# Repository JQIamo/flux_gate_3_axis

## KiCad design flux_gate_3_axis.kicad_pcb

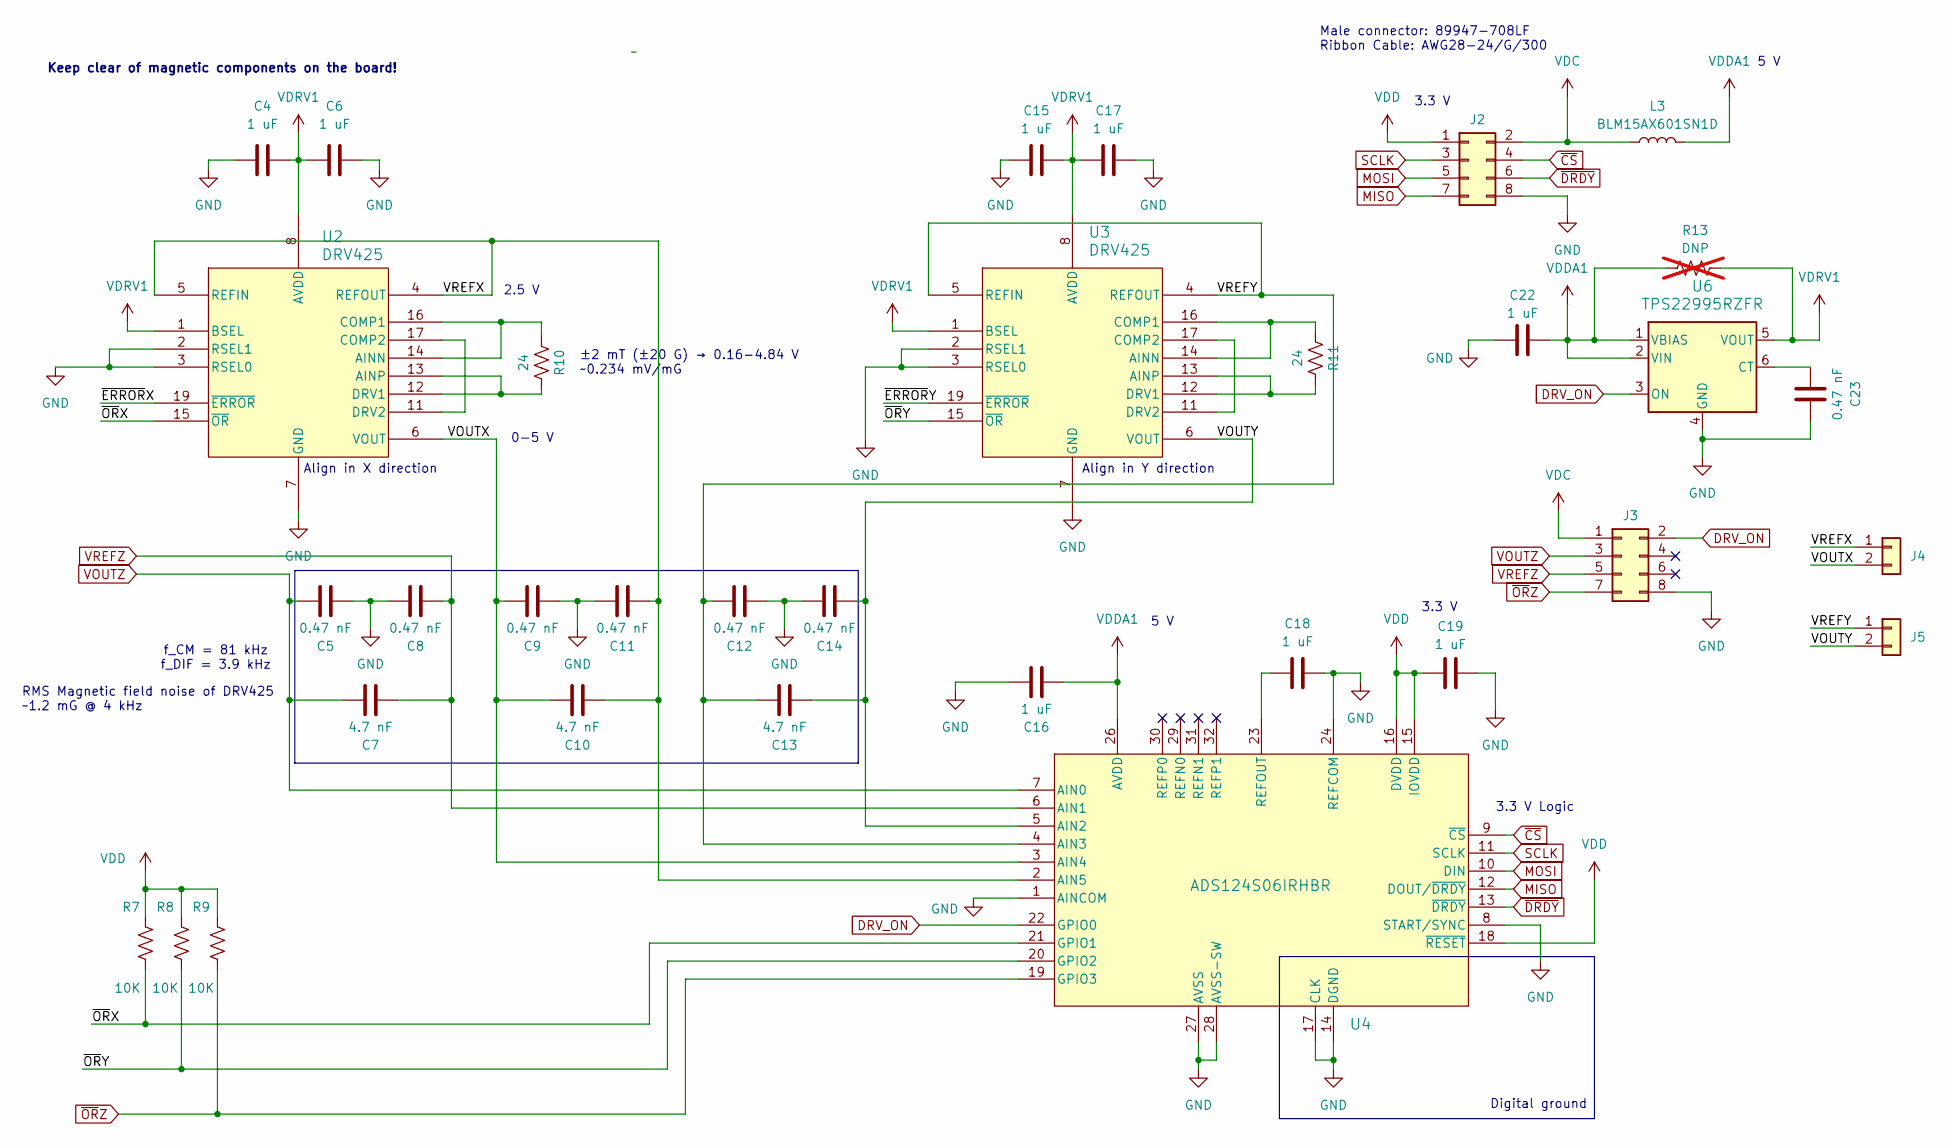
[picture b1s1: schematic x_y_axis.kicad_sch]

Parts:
C4, C6, C15, C16, C17, C18, C19, C22: 1 uF; C_0402_1005Metric; Digikey 490-10018-1-ND
C5, C8, C9, C11, C12, C14, C23: 0.47 nF; C_0402_1005Metric; Digikey 490-1297-1-ND
C7, C10, C13: 4.7 nF; C_0402_1005Metric; Digikey 490-GRM1555C1H472GE01DCT-ND
J2: Conn_02x04_Odd_Even; AMPHENOL_98464-G61-08LF; Digikey 609-6027-ND
J3: Conn_02x04_Odd_Even; PinHeader_2x04_P2.00mm_Vertical; Digikey A108094-ND
J4, J5: Conn_01x02; TestPoint_2Pads_Pitch2.54mm_Drill0.8mm
L3: BLM15AX601SN1D; L_0402_1005Metric; Digikey 490-5441-1-ND
R7, R8, R9: 10K; R_0402_1005Metric; Digikey 311-10KJRCT-ND
R10, R11: 24; R_0805_2012Metric; Digikey 13-RT0805BRD0724RLCT-ND
R13: DNP; R_0402_1005Metric; not fitted
U2, U3: DRV425; WQFN20_RTJ_TEX; Digikey 296-DRV425QWRTJRQ1CT-ND
U4: ADS124S06IRHBR; VQFN-32-1EP_5x5mm_P0.5mm_EP3.1x3.1mm; Digikey 296-ADS124S06IRHBRCT-ND
U6: TPS22995RZFR; WQFN6_RZF_TEX

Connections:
/x_y_axis/VOUTX: C9.1, C10.1, J4.2, U2.6 (VOUT), U4.3 (AIN4)
/x_y_axis/VOUTY: C13.2, C14.2, J5.2, U3.6 (VOUT), U4.5 (AIN2)
/x_y_axis/VREFX: C10.2, C11.2, J4.1, U2.4 (REFOUT), U2.5 (REFIN), U4.2 (AIN5)
/x_y_axis/VREFY: C12.1, C13.1, J5.1, U3.4 (REFOUT), U3.5 (REFIN), U4.4 (AIN3)
/x_y_axis/~ERRORX: U2.19 (~ERROR)
/x_y_axis/~ERRORY: U3.19 (~ERROR)
/x_y_axis/~ORX: R7.1, U2.15 (~OR), U4.21 (GPIO1)
/x_y_axis/~ORY: R8.1, U3.15 (~OR), U4.20 (GPIO2)
DRV_ON: J3.2, U4.22 (GPIO0), U6.3 (ON); also elsewhere on the board
GND: C4.1, C5.2, C6.1, C8.1, C9.2, C11.1, C12.2, C14.1, C15.1, C16.1, C17.1, C18.2, C19.2, C22.2, C23.1, J2.8, J3.8, U2.2 (RSEL1), U2.3 (RSEL0), U2.7 (GND), U2.10 (GND), U2.18 (GND), U2.20 (GND), U2.21 (GND), U3.2 (RSEL1), U3.3 (RSEL0), U3.7 (GND), U3.10 (GND), U3.18 (GND), U3.20 (GND), U3.21 (GND), U4.1 (AINCOM), U4.8 (START/SYNC), U4.14 (DGND), U4.17 (CLK), U4.24 (REFCOM), U4.27 (AVSS), U4.28 (AVSS-SW), U4.33 (PAD), U6.4 (GND); also elsewhere on the board
MISO: J2.7, U4.12 (DOUT/~DRDY); also elsewhere on the board
MOSI: J2.5, U4.10 (DIN); also elsewhere on the board
unnamed: R10.2, U2.14 (AINN), U2.16 (COMP1)
unnamed: R10.1, U2.12 (DRV1), U2.13 (AINP)
unnamed: U2.11 (DRV2), U2.17 (COMP2)
unnamed: R11.2, U3.14 (AINN), U3.16 (COMP1)
unnamed: R11.1, U3.12 (DRV1), U3.13 (AINP)
unnamed: U3.11 (DRV2), U3.17 (COMP2)
unnamed: C18.1, U4.23 (REFOUT)
unnamed: C23.2, U6.6 (CT)
SCLK: J2.3, U4.11 (SCLK); also elsewhere on the board
VDC: J2.2, J3.1, L3.2; also elsewhere on the board
VDD: C19.1, J2.1, R7.2, R8.2, R9.2, U4.15 (IOVDD), U4.16 (DVDD), U4.18 (~RESET); also elsewhere on the board
VDDA1: C16.2, C22.1, L3.1, R13.1, U4.26 (AVDD), U6.1 (VBIAS), U6.2 (VIN)
VDRV1: C4.2, C6.2, C15.2, C17.2, R13.2, U2.1 (BSEL), U2.8 (AVDD), U2.9 (AVDD), U3.1 (BSEL), U3.8 (AVDD), U3.9 (AVDD), U6.5 (VOUT)
VOUTZ: C5.1, C7.1, J3.3, U4.7 (AIN0); also elsewhere on the board
VREFZ: C7.2, C8.2, J3.5, U4.6 (AIN1); also elsewhere on the board
~CS: J2.4, U4.9 (~CS); also elsewhere on the board
~DRDY: J2.6, U4.13 (~DRDY); also elsewhere on the board
~ORZ: J3.7, R9.1, U4.19 (GPIO3); also elsewhere on the board

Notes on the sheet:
0-5 V
Align in X direction
Align in Y direction
RMS Magnetic field noise of DRV425 ~1.2 mG @ 4 kHz
5 V
3.3 V
Keep clear of magnetic components on the board!
Digital ground
2.5 V
3.3 V Logic
Male connector: 89947-708LF Ribbon Cable: AWG28-24/G/300
f_CM = 81 kHz f_DIF = 3.9 kHz
±2 mT (±20 G) → 0.16-4.84 V ~0.234 mV/mG

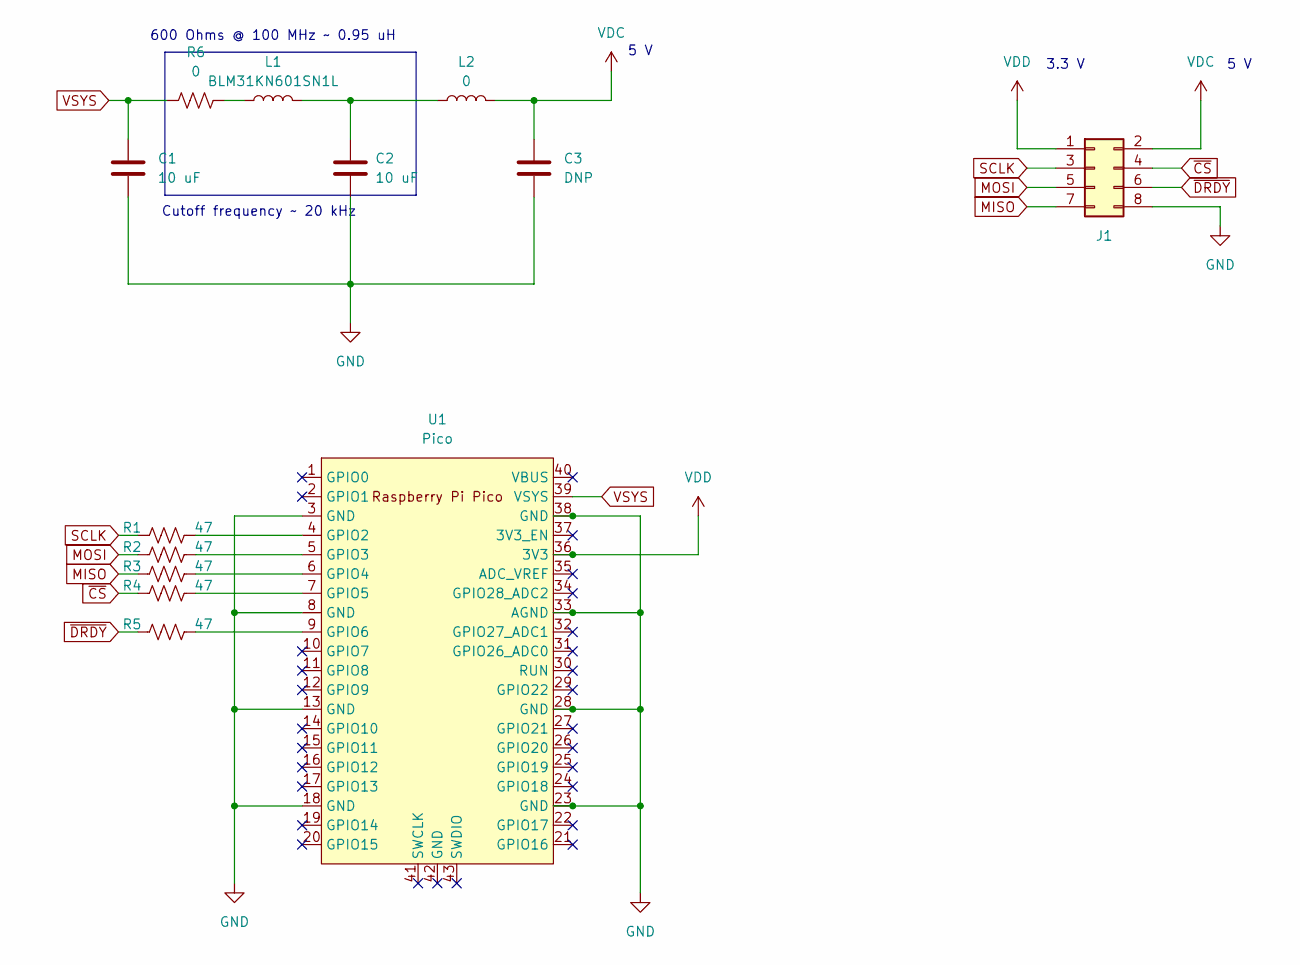
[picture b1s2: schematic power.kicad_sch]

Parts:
C1, C2: 10 uF; C_0603_1608Metric; Digikey 490-12323-1-ND
C3: DNP; C_0603_1608Metric
J1: Conn_02x04_Odd_Even; AMPHENOL_98464-G61-08LF; Digikey 609-6027-ND
L1: BLM31KN601SN1L; L_1206_3216Metric; Digikey 490-16533-1-ND
L2: 0; L_1206_3216Metric; Digikey 311-0.0ERCT-ND
R1, R2, R3, R4, R5: 47; R_0402_1005Metric; Digikey 311-47.0LRCT-ND
R6: 0; R_0805_2012Metric; Digikey 311-0.0ERCT-ND
U1: Pico; RPi_Pico_Connector

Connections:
GND: C1.2, C2.2, C3.2, J1.8, U1.3 (GND), U1.8 (GND), U1.13 (GND), U1.18 (GND), U1.23 (GND), U1.28 (GND), U1.33 (AGND), U1.38 (GND); also elsewhere on the board
MISO: J1.7, R3.1; also elsewhere on the board
MOSI: J1.5, R2.1; also elsewhere on the board
unnamed: C2.1, L1.2, L2.1
unnamed: L1.1, R6.2
unnamed: R1.2, U1.4 (GPIO2)
unnamed: R2.2, U1.5 (GPIO3)
unnamed: R3.2, U1.6 (GPIO4)
unnamed: R4.2, U1.7 (GPIO5)
unnamed: R5.2, U1.9 (GPIO6)
SCLK: J1.3, R1.1; also elsewhere on the board
VDC: C3.1, J1.2, L2.2; also elsewhere on the board
VDD: J1.1, U1.36 (3V3); also elsewhere on the board
VSYS: C1.1, R6.1, U1.39 (VSYS)
~CS: J1.4, R4.1; also elsewhere on the board
~DRDY: J1.6, R5.1; also elsewhere on the board

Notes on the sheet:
600 Ohms @ 100 MHz ~ 0.95 uH
Cutoff frequency ~ 20 kHz
5 V
3.3 V

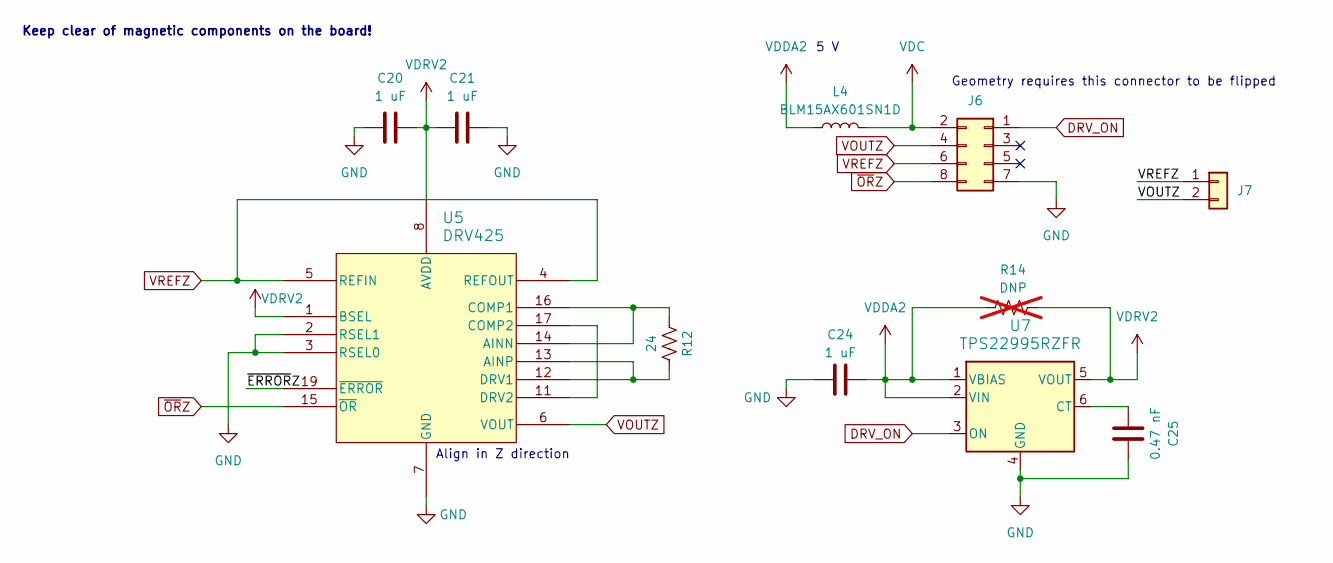
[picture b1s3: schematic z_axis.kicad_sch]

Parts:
C20, C21, C24: 1 uF; C_0402_1005Metric; Digikey 490-10018-1-ND
C25: 0.47 nF; C_0402_1005Metric; Digikey 490-1297-1-ND
J6: Conn_02x04_Odd_Even; PinHeader_2x04_P2.00mm_Vertical; Digikey 609-2574-ND
J7: Conn_01x02; TestPoint_2Pads_Pitch2.54mm_Drill0.8mm
L4: BLM15AX601SN1D; L_0402_1005Metric; Digikey 490-5441-1-ND
R12: 24; R_0805_2012Metric; Digikey 13-RT0805BRD0724RLCT-ND
R14: DNP; R_0402_1005Metric; not fitted
U5: DRV425; WQFN20_RTJ_TEX; Digikey 296-DRV425QWRTJRQ1CT-ND
U7: TPS22995RZFR; WQFN6_RZF_TEX

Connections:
/z_axis/~ERRORZ: U5.19 (~ERROR)
DRV_ON: J6.1, U7.3 (ON); also elsewhere on the board
GND: C20.1, C21.1, C24.2, C25.1, J6.7, U5.2 (RSEL1), U5.3 (RSEL0), U5.7 (GND), U5.10 (GND), U5.18 (GND), U5.20 (GND), U5.21 (GND), U7.4 (GND); also elsewhere on the board
unnamed: R12.2, U5.14 (AINN), U5.16 (COMP1)
unnamed: R12.1, U5.12 (DRV1), U5.13 (AINP)
unnamed: U5.11 (DRV2), U5.17 (COMP2)
unnamed: C25.2, U7.6 (CT)
VDC: J6.2, L4.2; also elsewhere on the board
VDDA2: C24.1, L4.1, R14.1, U7.1 (VBIAS), U7.2 (VIN)
VDRV2: C20.2, C21.2, R14.2, U5.1 (BSEL), U5.8 (AVDD), U5.9 (AVDD), U7.5 (VOUT)
VOUTZ: J6.4, J7.2, U5.6 (VOUT); also elsewhere on the board
VREFZ: J6.6, J7.1, U5.4 (REFOUT), U5.5 (REFIN); also elsewhere on the board
~ORZ: J6.8, U5.15 (~OR); also elsewhere on the board

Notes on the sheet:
Keep clear of magnetic components on the board!
Geometry requires this connector to be flipped
5 V
Align in Z direction

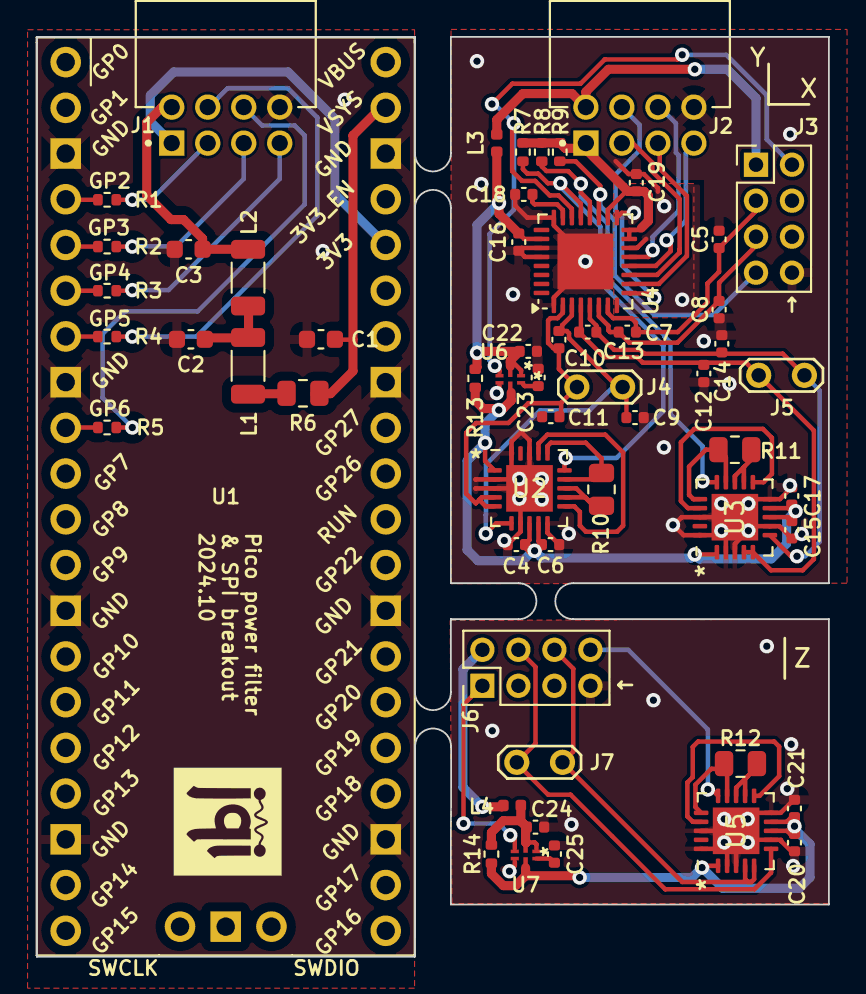
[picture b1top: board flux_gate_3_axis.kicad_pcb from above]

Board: 4 copper layers, 44.0 x 51.1 mm, 57 parts (0 on the bottom side), 42 nets.

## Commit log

2024-10-18 init commit
2024-10-18 removed useless files
2024-10-18 added link to github repo
2024-10-18 fixed silkscreen
2024-10-18 improved ground connectivity
